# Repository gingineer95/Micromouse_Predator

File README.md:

Kailey Smith
# Mircomouse Predator from Scratch

## Project Overview

The goal of this project was to design, construct, and control a small wheeled robot, completely from scratch. Dr. Malcolm MacIver’s lab is studying robot-rodent interactions and required a robot to act as a high-speed predator that will constantly try to discover, chase, and corner a mouse in a maze-like habitat. 

To achieve this, I drew knowledge from my previous mechatronics experience to build a motor control circuit, communicate wirelessly using a Digi XBee module radio, as well as create a custom PCB. I also took inspiration from the <a href="https://en.wikipedia.org/wiki/Micromouse" target="_blank" rel="noopener noreferrer">Half-Sized Micromouse Competition</a> for both mechanical and electrical design. 

**The end result:** a remote controlled differential drive robot. Below is a video of robot being given left and right DC commands. It shows the robot moving forward and backwards, turning in a circle, and lastly moving in a loop. Note: these are only feed-forward commands, feed-back control is needed for precise movement.

Please checkout my [portfolio post](https://gingineer95.github.io/2021/12/11/micromouse/) for more details. 

## Repo Hierarchy
MPLAB: Contains all C code, including programs used during breadboard testing and PCB testing.

Micromouse_solidworks_assembly: 3D modeled parts and assemblies.

Motor_Analysis: Contains a jupyter notebook in which I analyized different motors to use for the robot.

PCB_design: Contains all Eagle files, including libraries used and schematics/board desings

## Motor Analysis

My goal was to create a simulated “race” between a given brushed DC motor and the mice to find motors that ran faster than the mice. Dr. MaIver’s lab provided me with mouse trajectory and velocity data over time from their ongoing experiments. With this information to compare to, I needed to extrapolate equations to calculate a motor’s position and linear velocity over time given only a motor’s electrical specs. 

To model the motor’s behavior, I started using a simple equation that expresses input and outputs in terms of power below:

Where *I* is the current through the motor, *V* is the voltage across the motor,  and  stand for torque and angular velocity on the output shaft and R is the motor’s internal resistance. The left side of the equation accounts for the electrical input power into a motor, while the right side accounts for the mechanical output power and power expelled through heat dissipation. After substituting in the torque constant , then  for torque, and  for omega, I solved for an equation that is represented by the 1st and 2nd and 1st order differentials of displacement over time:

Once I had a function that was dependent on displacement over time, I was able to run the “race” simualtions. In order to get the robots linear and velocity displacement over time to compare to they mice, solved the equation for *x(t)* as well as *x'(t)*:

Using the equations, I compared several motors to the mice by creating graphs such as the two below. The blue line represents the motor’s data while the green line represents a mouse.

I also examined each motor’s torque-speed curve to ensure that a motor’s anticipated torque outputs were within the continuous operating region of that motor. Using all graphs I was able to eliminate several motors while still having a couple of viable motors to choose from. 

My final motor selection came down to weight and size. For this entire system, the motors and battery we’re the largest and heaviest components. Therefore I wanted the smallest and lightest option of both. This meant choosing a 1 cell battery and therefore a motor that only needed up to 3.7V to operate. After doing some initial mechanical modeling, I chose a light and small motor that fit the design configuration I was looking for. 

## PCB Design

Once the critical parts were chosen, it was time to order all the other circuit components so I could start breadboarding and testing the circuit before ordering a custom PCB. I chose to use a PIC32 microcontroller since I had previous experience with these chips and there were a couple on hand to get started with quickly. Along those lines, I also chose to use the TI DRV8833 motor drivers. As a safety precaution, I added IR distance sensors to detect objects and avoid collisions. The last key component to this circuit was the Digi XBee 3 802.15.4 module which I used to communicate wirelessly with the robot. 

In order to integrate all the circuit components into a small area on the robot, a custom PCB was necessary. After I confirmed that my circuit worked on the breadboard, I had confidence that I could design a functional PCB. 

My initial thought was to use the PCB as a chassis component, as many of the Micromouse robots do. However, the MacIver lab uses a camera system above their habitat to track the mice and robot. And in order to detect, track, and determine the orientation of the robot, 3 red LEDs need to form an isosceles triangle on top of the robot. Given that, it was simple to rework the mechanical design so the PCB was the top-most component.

As with all PCB prototyping, this was a very iterative process, especially considering how many components needed to fit in such a small space. The dimensions of the PCB were determined by the footprint of the robot, which in turn was driven by the length of the motors. I was able to fit 35 components in a 46cm x 34cm space as pictured below.

<div align="center">View from OSHPark</div>

Once the boards were manufactured, I soldered all the individual components myself using a microscope. I quickly realized I couldn’t program my microcontroller. I did a continuity test to identify the issue and discovered I didn’t have common ground across all the components. To get my PCB up and running as quickly as possible, I soldered jumper wires to all components that needed common ground. After that I was able to program the PIC and confirm that all my other connections were correct. I designed a new board with common ground for future use. 

## Mechanical Design

Below are images of the finalized, differential drive robot that I modeled in Soldiworks and then 3D printed.

<div align="center">Final design, 5cm wide by 5.5cm long</div>

I started with a four wheel configuration like many of the Micromouse designs. But after some testing, I discovered that the flooring in the MacIver lab habitat has a much higher coefficient of friction than the flooring used in the Micromouse competitions. I decided to remove two wheels and switch the tire material to a harder rubber o-ring which were skinner and therefore had smaller areas of contact to make turns easier. The thinner wheels also had the benefit of making the overall width of the robot smaller.

## Next Steps

As a safety feature the next immediate step will be incorporating the IR distance sensors as object avoidance / collision detection. I have already accounted for the sensors in my PCB, so all there is left to do is mount the hardware and implement functionality onto the microchip such that the robot stops if it senses that an object is too close. 

Given that there is a mechanically and electrically sound design, the next control steps are to add a PID controller. The MacIver lab is able to track the robot's location as it moves throughout the habitat. With that information, a position feedback controller can be implemented per the block diagram below. 

Once the PID controller is squared away, the final step for autonomous navigation will be to create a path planning algotihm. This algorithm will recevice a mouse location and plan a route from the robot's location to the mouse while avoiding all obstacles. With that, the predator robot will be fully operational!
Final Project for MSR program at Northwestern.

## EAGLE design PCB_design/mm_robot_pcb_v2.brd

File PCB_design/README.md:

Kailey Smith
# Mircomouse Predator from Scratch

## PCB Design

In this directory, I added my custom built library from EAGLE. There are several iterations of my PCB here, the version I'm currently using on the robot is v4, but this version does not have common ground. In the future, v6 should be used.

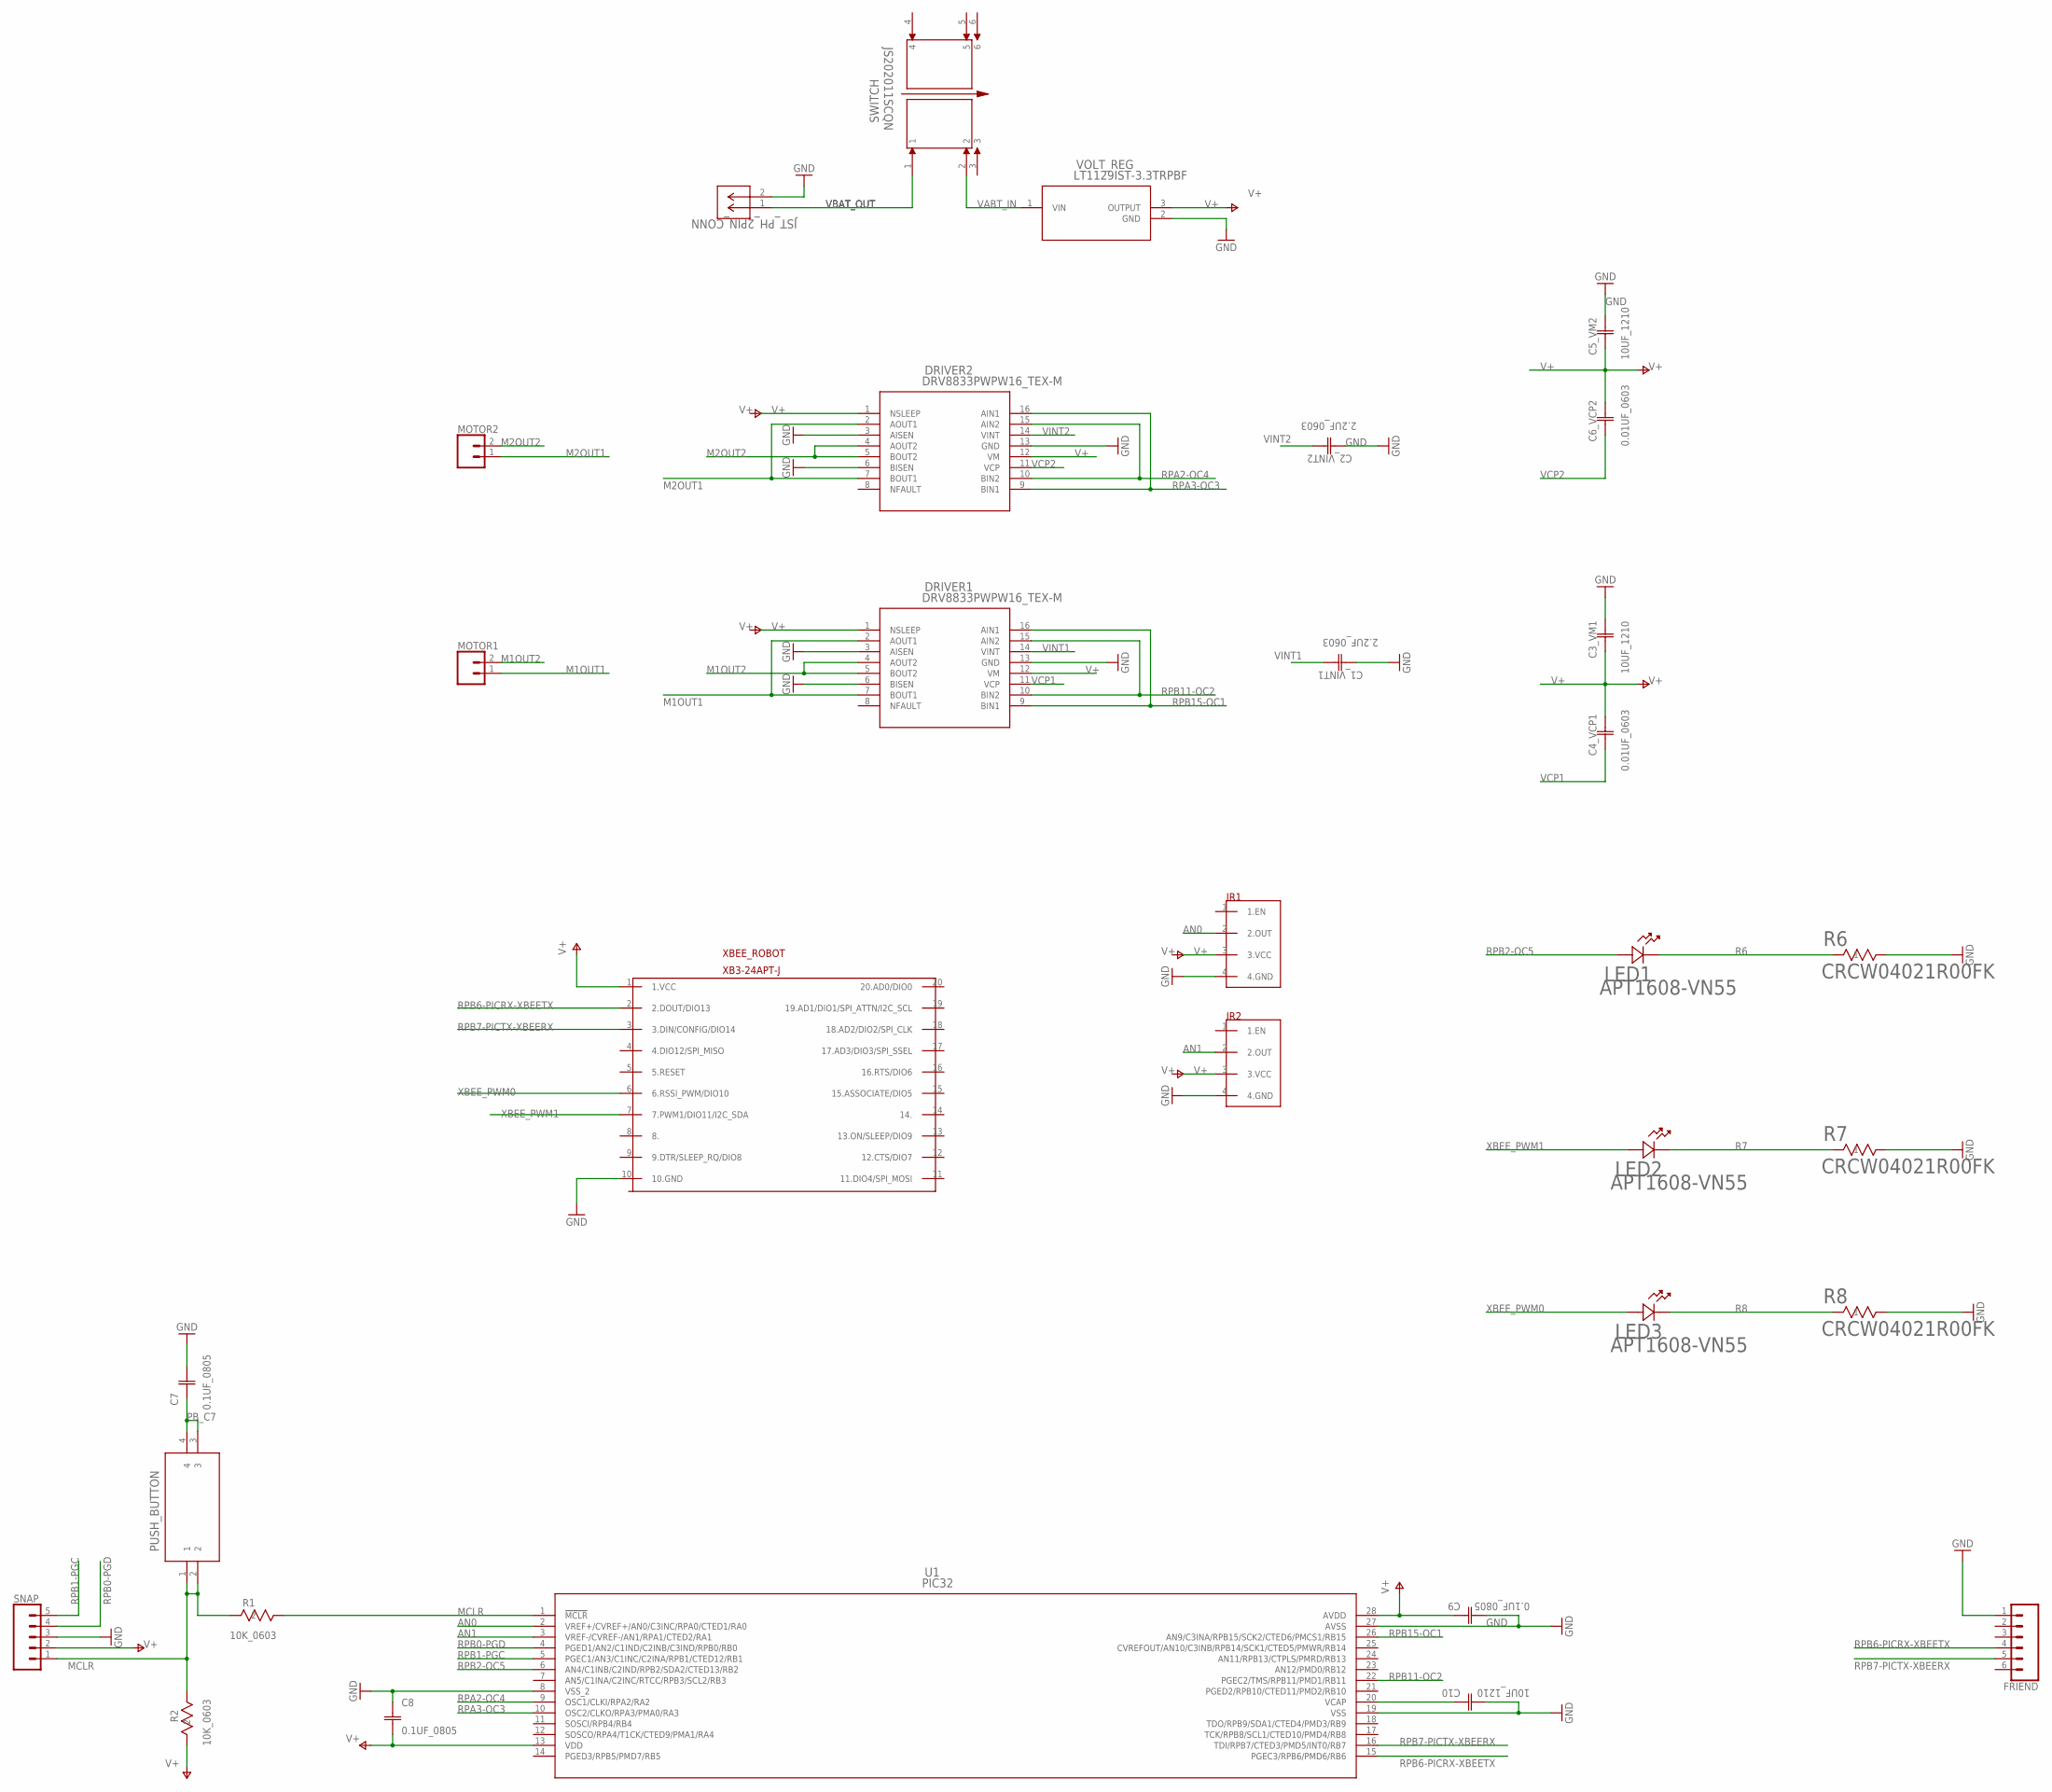
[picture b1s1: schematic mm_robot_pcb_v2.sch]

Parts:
C1_VINT1, C2_VINT2: 2.2UF_0603; CAP_CL10_SAM
C3_VM1, C5_VM2, C10: 10UF_1210; CAP_TPS_B_AVX
C4_VCP1, C6_VCP2: 0.01UF_0603; CAP_01UF_0603_X7R_G_AVX
C7, C8, C9: 0.1UF_0805; CAP_C2012X7R2A104K125AA_TDK
DRIVER1, DRIVER2: DRV8833PWPW16_TEX-M; PW16_TEX-M
FRIEND: CONN_06LOCK; 1X06_LOCK
IR1, IR2: GP2Y0A60SZLF; 1X04
JST_PH_2PIN_CONN: 1769; CONN_1769_ADA
LED1, LED2, LED3: APT1608-VN55; LED_APT1608_KNB
MOTOR1, MOTOR2: CONN_02; 1X02
R1, R2: 10K_0603; RES0603_CRG_TYCO_TYC
R6, R7, R8: CRCW04021R00FK; RES_CRCW0402_VIS
SNAP: CONN_05; 1X05
SWITCH: JS202011SCQN; SW_JS202011SCQN
U1: PIC32; SSOP28_MC_MCH
U2: PUSH_BUTTON; SMT_FS
VOLT_REG: LT1129IST-3.3TRPBF; SOT-223_ST_LIT
XBEE_ROBOT: XB3-24APT-J

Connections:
AN0: IR1.2 (2.OUT), U1.2 (VREF+/CVREF+/AN0/C3INC/RPA0/CTED1/RA0)
AN1: IR2.2 (2.OUT), U1.3 (VREF-/CVREF-/AN1/RPA1/CTED2/RA1)
GND: C1_VINT1.1, C2_VINT2.1, C3_VM1.2 (12), C5_VM2.2 (12), C7.2, C8.1, C9.1, C10.1 (11), DRIVER1.3 (AISEN), DRIVER1.6 (BISEN), DRIVER1.13 (GND), DRIVER2.3 (AISEN), DRIVER2.6 (BISEN), DRIVER2.13 (GND), FRIEND.1, IR1.4 (4.GND), IR2.4 (4.GND), JST_PH_2PIN_CONN.2, R6.2, R7.2, R8.2, SNAP.3, U1.8 (VSS_2), U1.19 (VSS), U1.27 (AVSS), VOLT_REG.2 (GND), XBEE_ROBOT.10 (10.GND)
M1OUT1: DRIVER1.2 (AOUT1), DRIVER1.7 (BOUT1), MOTOR1.1
M1OUT2: DRIVER1.4 (AOUT2), DRIVER1.5 (BOUT2), MOTOR1.2
M2OUT1: DRIVER2.2 (AOUT1), DRIVER2.7 (BOUT1), MOTOR2.1
M2OUT2: DRIVER2.4 (AOUT2), DRIVER2.5 (BOUT2), MOTOR2.2
MCLR: R1.1, R1.2, R2.1, SNAP.1, U1.1 (!MCLR), U2.1, U2.2
unnamed: C10.2 (12), U1.20 (VCAP)
PB_C7: C7.1, U2.3, U2.4
R6: LED1.1, R6.1
R7: LED2.1, R7.1
R8: LED3.1, R8.1
RPA2-OC4: DRIVER2.10 (BIN2), DRIVER2.15 (AIN2), U1.9 (OSC1/CLKI/RPA2/RA2)
RPA3-OC3: DRIVER2.9 (BIN1), DRIVER2.16 (AIN1), U1.10 (OSC2/CLKO/RPA3/PMA0/RA3)
RPB0-PGD: SNAP.4, U1.4 (PGED1/AN2/C1IND/C2INB/C3IND/RPB0/RB0)
RPB1-PGC: SNAP.5, U1.5 (PGEC1/AN3/C1INC/C2INA/RPB1/CTED12/RB1)
RPB2-OC5: LED1.2, U1.6 (AN4/C1INB/C2IND/RPB2/SDA2/CTED13/RB2)
RPB6-PICRX-XBEETX: FRIEND.4, U1.15 (PGEC3/RPB6/PMD6/RB6), XBEE_ROBOT.2 (2.DOUT/DIO13)
RPB7-PICTX-XBEERX: FRIEND.5, U1.16 (TDI/RPB7/CTED3/PMD5/INT0/RB7), XBEE_ROBOT.3 (3.DIN/CONFIG/DIO14)
RPB11-OC2: DRIVER1.10 (BIN2), DRIVER1.15 (AIN2), U1.22 (PGEC2/TMS/RPB11/PMD1/RB11)
RPB15-OC1: DRIVER1.9 (BIN1), DRIVER1.16 (AIN1), U1.26 (AN9/C3INA/RPB15/SCK2/CTED6/PMCS1/RB15)
V+: C3_VM1.1 (11), C4_VCP1.2, C5_VM2.1 (11), C6_VCP2.2, C8.2, C9.2, DRIVER1.1 (NSLEEP), DRIVER1.12 (VM), DRIVER2.1 (NSLEEP), DRIVER2.12 (VM), IR1.3 (3.VCC), IR2.3 (3.VCC), R2.2, SNAP.2, U1.13 (VDD), U1.28 (AVDD), VOLT_REG.3 (OUTPUT), XBEE_ROBOT.1 (1.VCC)
VABT_IN: SWITCH.2, VOLT_REG.1 (VIN)
VBAT_OUT: JST_PH_2PIN_CONN.1, SWITCH.1
VCP1: C4_VCP1.1, DRIVER1.11 (VCP)
VCP2: C6_VCP2.1, DRIVER2.11 (VCP)
VINT1: C1_VINT1.2, DRIVER1.14 (VINT)
VINT2: C2_VINT2.2, DRIVER2.14 (VINT)
XBEE_PWM0: LED3.2, XBEE_ROBOT.6 (6.RSSI_PWM/DIO10)
XBEE_PWM1: LED2.2, XBEE_ROBOT.7 (7.PWM1/DIO11/I2C_SDA)

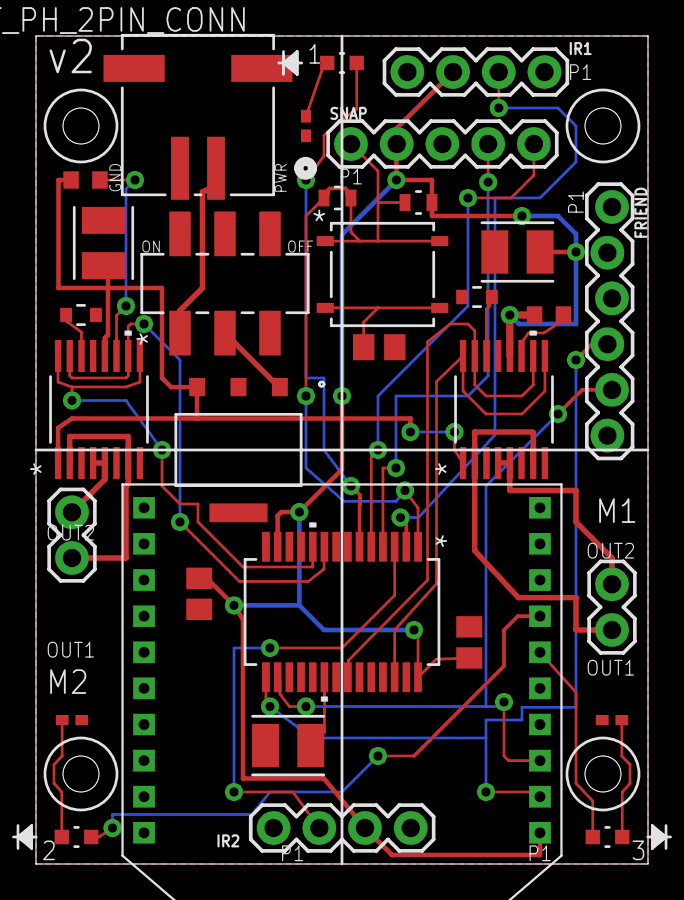
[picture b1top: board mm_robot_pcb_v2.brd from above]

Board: 2 copper layers, 34.0 x 46.0 mm, 32 parts (0 on the bottom side), 31 nets.

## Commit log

2021-05-14 Added a new file where I'm reworking my notebook
2021-05-18 Working on my simulations. I'm able to elimate motors that cant meet the power requirements, now I need to look at different gear ratios and how those affect the trajectories
2021-05-19 Updated my motor selection notebook with a reccomendation of the DCX12L
2021-05-21 Completed motor analysis based on mouse data and made motor reccomendations
2021-05-21 Renamed an old file
2021-05-26 Updated analysis with gear and battery calculations
2021-05-31 Little update
2021-06-02 Added some analysis for the smaller Micromouse motors
2021-06-02 Updated my tiny motor analysis
2021-06-08 Adding my parts from EAGLE for seafekeeping. Note, this library was made for schematic purposes only, the footprints are not accurate
2021-06-08 Added updated library and also a schematic for the motor driving ciruit
2021-11-12 Re-organized directory. Added Eagle boards and schematics for my PCB user the folder 'PCB_design'. Added all C code written until now under 'MPLAB'. Moved all previous motor analysis files under 'Mot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
2021-11-12 Added README
2021-11-13 Turning in MPLAB/140_PCB_TEST, but not great. Right now both wheels turn forward. Fix so only one wheel is forward and one is back
2021-11-13 Fixed 130 file to turn while wheels move backwards
2021-11-29 Adding updated MPLAB code
2021-12-10 Added all soldiworks models
2021-12-11 added READMEs
2021-12-11 Edited readme
2021-12-11 Very pretty readme
2021-12-11 Linked portfolio to readme
2021-12-11 Re-organized a bit
2021-12-11 Whoop, made my portfolio link an image
2021-12-11 Removed some old irrelevant comment in README
2021-12-11 Finished all the READMEs for all folders
2021-12-12 Fixed broken link to portfolio post
2022-06-01 Renamed PCB files so they're numbered correctly

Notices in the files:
parts and their libraries:
COPYRIGHT: Copyright (C) 2021 Ultra Librarian. All rights reserved.
